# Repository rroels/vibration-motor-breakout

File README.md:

# 2-in-1 Vibration Motor Breakout Board

> [!WARNING]
> The information and material (code, designs, files, ...) are provided "AS IS". We make no representation or warranty of any kind, express or implied, regarding the accuracy, adequacy, validity, reliability, availability, or completeness of any information or material. Use this at your own risk.

> [!WARNING]
> At the time of writing this PCB has not even been produced yet, and as such, it has not even been tested yet! Once it has been properly tested, I will confirm that everything works as expected.

## Introduction

This is a breakout board for small vibration motors, such as those used in (smart)watches.

It is 2-in-1, because it provides two ways to interface with the motor:

* via PWM
* via the Texas Instruments DRV2625 Haptic Driver IC

## Change Log

* v1.0
  * Initial design 

## Design Considerations

* NRST is not connected to the chip, as I was not able to route the NRST pin out of the tiny BGA footprint. This is however an optional feature anyway. 

## Schematics 

## How to Obtain the Physical PCB

The Gerber file is in this repository (`kicad/gerber/vibration-motor.zip`). Simply upload this file a PCB manufacturer of your choice (JLPCB, PCBWay, ...), and you they will make it for you for as low as \$5 for 5 pieces (with the cheapest shipping option, which can take a few weeks).

For JLCPCB, select the order number option where they will replace "JLCJLCJLCJLC" on the board with the actual order number.

> [!WARNING]
> Note that will still have to solder the components onto the PCB yourself!

## How to Edit Design

Everything you need to edit this design in KiCad 8 is included in the repository.

However, this project uses symbols, footprints and 3D models from [Component Search Engine](https://componentsearchengine.com/). Their license allows us to do pretty much whatever we want with them, except redistributing them. For this reason I can't include them in this repository.

If you would like to edit the design yourself, you will need to download the following component libraries from [https://componentsearchengine.com/](https://componentsearchengine.com/) (it's free!):

* [https://componentsearchengine.com/part-view/DRV2625YFFT/Texas%20Instruments](https://componentsearchengine.com/part-view/DRV2625YFFT/Texas%20Instruments)

From the downloaded zip files, move the content of the `KiCad` and `3D` subfolders into the project structure, so that the end-result looks like this:

The KiCad project is configured to look for these files in these locations, using relative paths, so no changes to the project itself are required.	

## Sources

* [https://www.nordicsemi.com/Products/nPM1300](https://www.nordicsemi.com/Products/nPM1300)
* [https://docs.nordicsemi.com/category/npm1300-category](https://docs.nordicsemi.com/category/npm1300-category)
* [https://shop.pimoroni.com/products/drv2605l-linear-actuator-haptic-breakout](https://shop.pimoroni.com/products/drv2605l-linear-actuator-haptic-breakout)
* [https://hackaday.io/project/169967-nrf52-smartwatch](https://hackaday.io/project/169967-nrf52-smartwatch)
* [https://github.com/sqfmi/watchy-hardware/blob/v3.0/WatchySchematic.pdf](https://github.com/sqfmi/watchy-hardware/blob/v3.0/WatchySchematic.pdf)
* [https://www.hobbyelectronica.nl/product/tril-vibratie-dc-motor-module-v3-7-5-3/](https://www.hobbyelectronica.nl/product/tril-vibratie-dc-motor-module-v3-7-5-3/)
* [https://www.ineedmotors.com/news/how-to-build-a-vibration-motor-circuit-34060799.html](https://www.ineedmotors.com/news/how-to-build-a-vibration-motor-circuit-34060799.html)
* [https://www.precisionmicrodrives.com/ab-001-discrete-driver-circuits-for-vibration-motors](https://www.precisionmicrodrives.com/ab-001-discrete-driver-circuits-for-vibration-motors)

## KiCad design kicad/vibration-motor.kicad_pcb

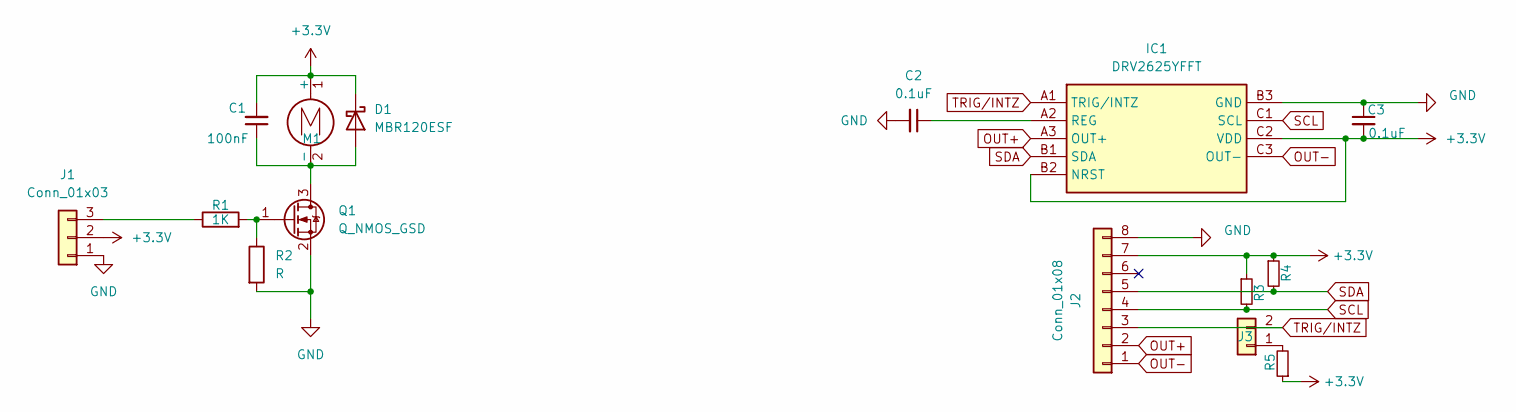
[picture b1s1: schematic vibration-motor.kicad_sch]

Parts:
C1: 100nF; C_0603_1608Metric_Pad1.08x0.95mm_HandSolder
C2, C3: 0.1uF; C_0603_1608Metric_Pad1.08x0.95mm_HandSolder
D1: MBR120ESF; D_SOD-123F
IC1: DRV2625YFFT; BGA9C40P3X3_147X133X62; Manufacturer_Part_Number DRV2625YFFT; Mouser Part Number 595-DRV2625YFFT
J1: Conn_01x03; PinHeader_1x03_P2.54mm_Vertical
J2: Conn_01x08; PinHeader_1x08_P2.54mm_Vertical
J3: Conn_01x02; PinHeader_1x02_P2.54mm_Vertical
M1: Motor_DC; PinHeader_1x02_P2.54mm_Vertical
Q1: Q_NMOS_GSD; TSOT-23_HandSoldering
R1: 1K; R_0603_1608Metric_Pad0.98x0.95mm_HandSolder
R2: R; R_0603_1608Metric_Pad0.98x0.95mm_HandSolder
R3, R4, R5: R_Small; R_0603_1608Metric_Pad0.98x0.95mm_HandSolder

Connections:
+3.3V: C1.2, C3.2, D1.1 (K), IC1.B2 (NRST), IC1.C2 (VDD), J1.2, J2.7, M1.1 (+), R3.1, R4.1, R5.1
GND: C2.2, C3.1, IC1.B3 (GND), J1.1, J2.8, Q1.2 (S), R2.2
unnamed: C1.1, D1.2 (A), M1.2 (-), Q1.3 (D)
unnamed: C2.1, IC1.A2 (REG)
unnamed: J1.3, R1.1
unnamed: J3.1, R5.2
unnamed: Q1.1 (G), R1.2, R2.1
OUT+: IC1.A3 (OUT+), J2.2
OUT-: IC1.C3 (OUT-), J2.1
SCL: IC1.C1 (SCL), J2.4, R3.2
SDA: IC1.B1 (SDA), J2.5, R4.2
TRIG/INTZ: IC1.A1 (TRIG/INTZ), J2.3, J3.2

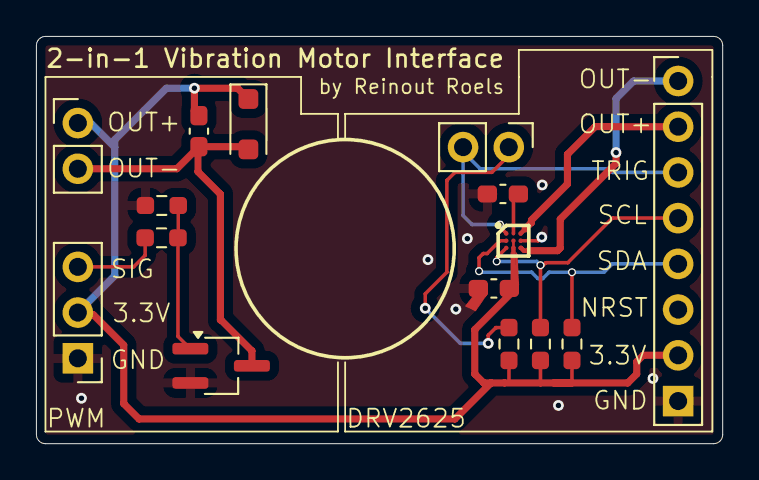
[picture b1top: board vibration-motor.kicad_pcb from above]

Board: 2 copper layers, 38.1 x 22.6 mm, 15 parts (0 on the bottom side), 12 nets.

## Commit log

2024-09-28 update schematics
